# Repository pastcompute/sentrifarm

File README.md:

# Farmer Stay In bed?

This is the main git repository for our entry into the 2015 hackaday prize.
For background see [the Sentrifarm project page on hackaday.io](http://hackaday.io/project/4758).

## Hackaday Prize Entry Qualifications

* [Project discussion](https://hackaday.io/project/4758)
* 2-minute [Quarter Final Submission Video](https://www.youtube.com/watch?v=L6NtuzwXCsY)
* Artist [impression](media/ArtisticImpression.png)
* [Project logs](https://hackaday.io/project/4758)
* [System design diagram](media/architecturediagramv0.2.svg)
* [System design - operational concept](OperationalConcept.md)
* [System design - component assembly](ComponentsAndAssembly.md)
* [TODO List](TODO.md)

## Licenses

* Hardware designs released under Creative Commons CC-BY-SA.
* Source code released under GPL v3 except where existing imported components are otherwise identified as being used under other licenses such as MIT, BSD, etc.
* Clipart in diagrams obtained from open / CC license sources : open office gallery, openclipart.com
* Our own photos and diagrams and videos under CC-BY-NC
* We reserve the right to dual-license software that we developed under alternative licenses

### Third party software components incorporated into the repository

* mqttsn-messages.cpp - MIT license

### Third party software components incorporated into the repository as a submodule

* Adafruit arduino sensor library - Apache license
* Adafruit BMP085 library - open source unspecified
* Arduino MQTTSN library - MIT license
* Arduino DHT11 library - MIT license
* Frankenstein & Antares - GPL licensed ESP8266 framework. Note, not actively used at present tie but this may change.

### Third party software components submodules or cloned and binaries cross-compiled during the build

* openwrt - linux distribution - distribution is GPL, components are their respective open source licenses
* c-ares - library used by mosquitto; MIT license
* mosquitto - MQTT client tools and library; used under Eclipse Distribution License (not the EPL)
* mqtt-sn-tools - MQTT-SN client tools; BSD-like license
* RSMB - MQTT and MQTT-SN broker; Eclipse Distribution License
* libsocket++ - C++ socket library; BSD license

The following third party software components are then dynamically linked to sentrifarm software:

libmosquitto - dynamically linked, thus used as allowed under the terms of the EDLv1.0

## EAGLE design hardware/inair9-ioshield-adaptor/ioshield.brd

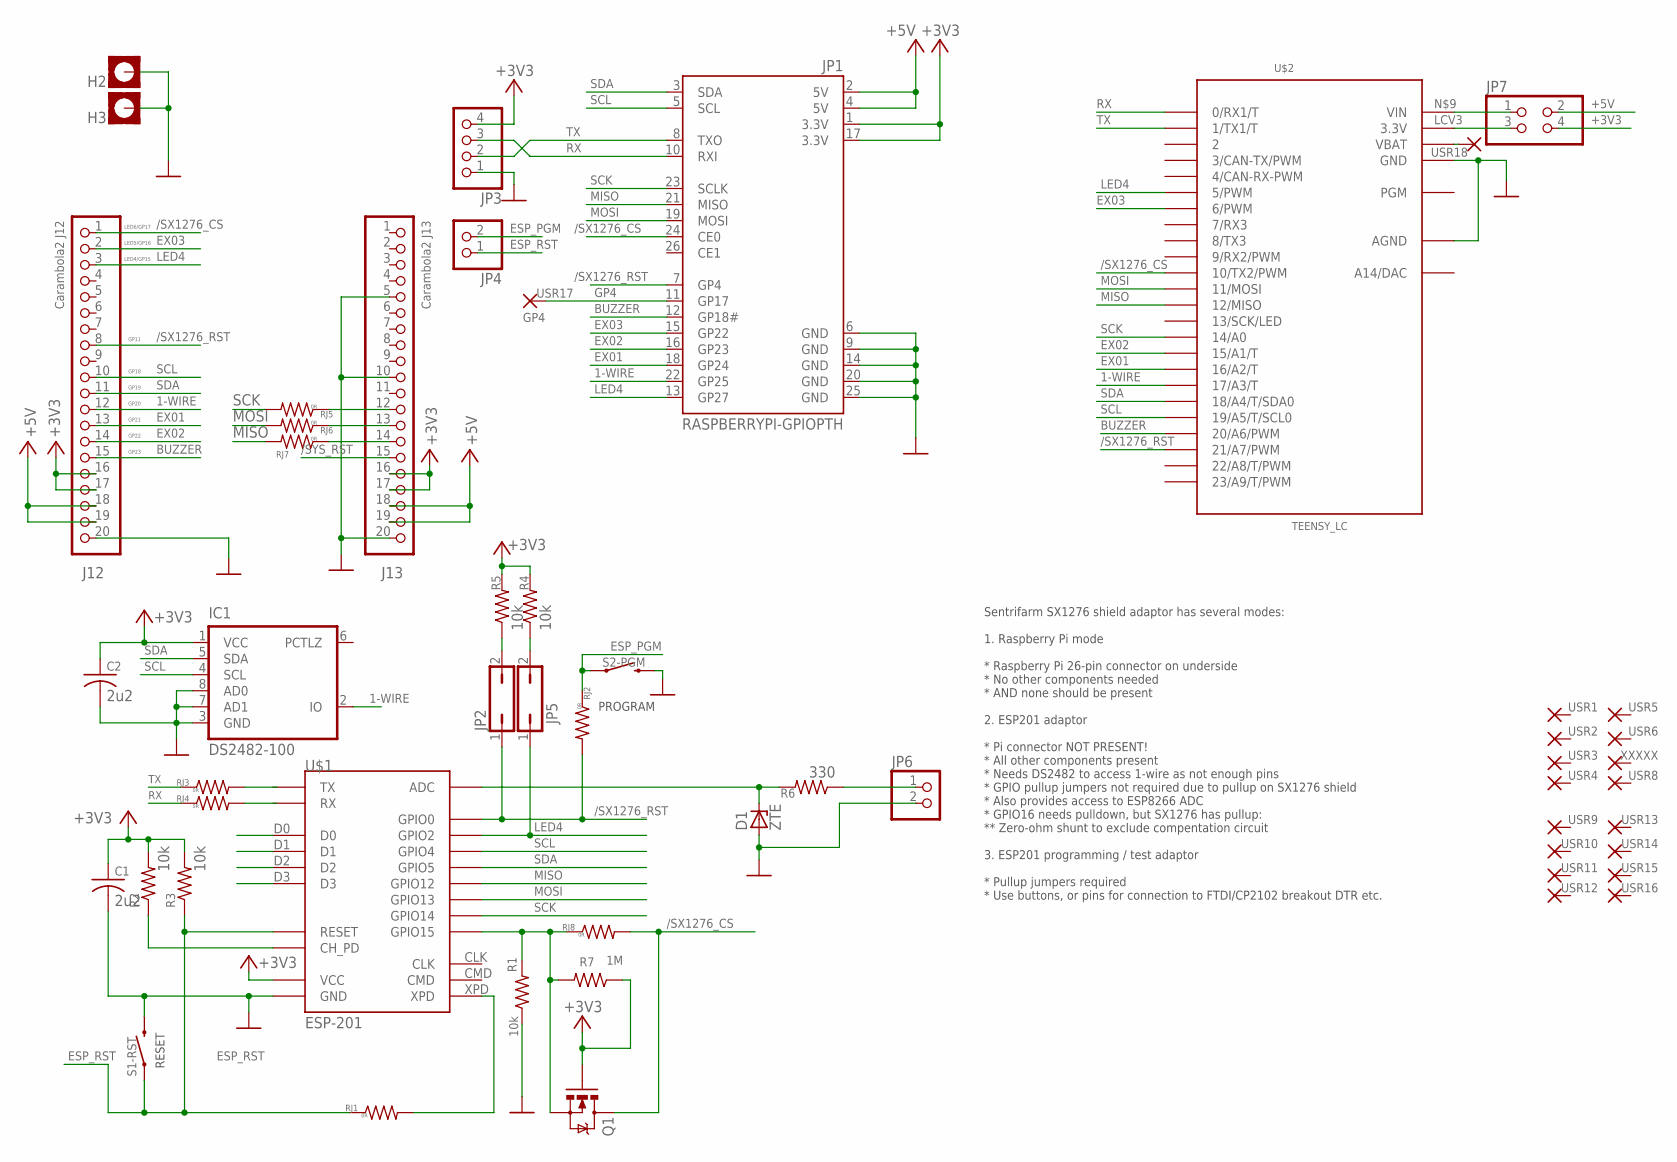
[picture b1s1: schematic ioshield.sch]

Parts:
C1, C2: 2u2; C1206
D1: ZTE; DO35Z10
H2, H3: MOUNT-PAD-SQUARE3.2; 3,2-PAD-SQUARE
IC1: DS2482-100; SO08
J12: Carambola2 J12; 1X20
J13: Carambola2 J13; 1X20
JP1: RASPBERRYPI-GPIOPTH; 2X13-SHROUDED
JP2, JP5: JP1Q; JP1
JP3: PINHD-1X4; 1X04
JP4, JP6: PINHD-1X2; 1X02
JP7: PINHD-2X2; 2X02
Q1: MOSFET-NCHANNEL2N7000; TO-92
R1, R2, R3, R4, R5: 10k; M1206
R6: 330; M1206
R7: 1M; M1206
RJ1, RJ2, RJ3, RJ4, RJ5, RJ6, RJ7, RJ8: 0R; M1206
S1-RST, S2-PGM: SWITCH-MOMENTARY-2PTH; TACTILE-PTH
U$1: ESP-201
U$2: TEENSY_LC; TEENSY_3.1_BASIC
USR1, USR2, USR3, USR4, USR5, USR6, USR8, USR9, USR10, USR11, USR12, USR13, USR14, USR15, USR16, USR18: 1,6/0,8
USR17: GP4; 1,6/0,8
XXXXX: 1,6/0,8

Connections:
1-WIRE: IC1.2 (IO), J12.12, JP1.22 (GP25), U$2.17/A3 (17/A3/T)
+3V3: C1.1, C2.1, IC1.1 (VCC), J12.16, J12.17, J13.16, J13.17, JP1.1 (3.3V), JP1.17 (3.3V), JP3.4, JP7.4, Q1.2 (G), R2.2, R3.2, R4.2, R5.2, R7.1, U$1.3V3 (VCC), U$1.3V3_2 (VCC), U$1.3V3_3 (VCC)
+5V: J12.18, J12.19, J13.18, J13.19, JP1.2 (5V), JP1.4 (5V), JP7.2
/SX1276_CS: J12.1, JP1.24 (CE0), Q1.3 (D), RJ8.2, U$2.10 (10/TX2/PWM)
/SX1276_RST: J12.8, JP1.7 (GP4), JP2.1, RJ2.2, U$1.GPIO0, U$2.21/A7 (21/A7/PWM)
/SYS_RST: J13.15
BUZZER: J12.15, JP1.12 (GP18#), U$2.20/A6 (20/A6/PWM)
CH_PD: R2.1, U$1.CH_PD
ESP_ADC: D1.C, R6.2, U$1.ADC
ESP_GPIO15: Q1.1 (S), R1.2, R7.2, RJ8.1, U$1.GPIO15
ESP_PGM: JP4.2, RJ2.1, S2-PGM.1
ESP_RST: JP4.1, R3.1, RJ1.1, S1-RST.1, U$1.RST (RESET)
EX01: J12.13, JP1.18 (GP24), U$2.16/A2 (16/A2/T)
EX02: J12.14, JP1.16 (GP23), U$2.15/A1 (15/A1/T)
EX03: J12.2, JP1.15 (GP22), U$2.6 (6/PWM)
GND: C1.2, C2.2, D1.A, H2.B3,2, H3.B3,2, IC1.3 (GND), IC1.7 (AD1), IC1.8 (AD0), J12.20, J13.5, J13.10, J13.20, JP1.6 (GND), JP1.9 (GND), JP1.14 (GND), JP1.20 (GND), JP1.25 (GND), JP3.1, JP6.2, R1.1, S1-RST.3 (2), S2-PGM.3 (2), U$1.GND, U$1.GND_2 (GND), U$1.GND_3 (GND), U$2.AGND, U$2.GND, U$2.GND1 (GND)
GP4: JP1.11 (GP17), USR17.1
LCV3: JP7.3, U$2.3.3V, U$2.3.3V1 (3.3V)
LED4: J12.3, JP1.13 (GP27), JP5.1, U$1.GPIO2, U$2.5 (5/PWM)
MISO: JP1.21 (MISO), RJ7.2, U$1.GPIO12, U$2.12 (12/MISO)
MOSI: JP1.19 (MOSI), RJ6.2, U$1.GPIO13, U$2.11 (11/MOSI)
unnamed: JP2.2, R5.1
unnamed: JP5.2, R4.1
unnamed: JP6.1, R6.1
unnamed: U$2.VBAT, USR18.1
unnamed: JP7.1, U$2.VIN
NXXX1: J13.12, RJ5.1
NXXX2: J13.13, RJ6.1
NXXX3: J13.14, RJ7.1
RX: JP1.10 (RXI), JP3.3, RJ4.1, U$2.0 (0/RX1/T)
SCK: JP1.23 (SCLK), RJ5.2, U$1.GPIO14, U$2.14/A0
SCL: IC1.4 (SCL), J12.10, JP1.5 (SCL), U$1.GPIO4, U$2.19/A5 (19/A5/T/SCL0)
SDA: IC1.5 (SDA), J12.11, JP1.3 (SDA), U$1.GPIO5, U$2.18/A4 (18/A4/T/SDA0)
TX: JP1.8 (TXO), JP3.2, RJ3.1, U$2.1 (1/TX1/T)
XPD: RJ1.2, U$1.XPD

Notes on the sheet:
LED6/GP17
GP18
GP19
GP20
GP21
GP22
GP23
LED5/GP16
LED4/GP15
GP11
Sentrifarm SX1276 shield adaptor has several modes: 1. Raspberry Pi mode * Raspberry Pi 26-pin connector on underside * No other components needed * AND none should be present 2. ESP201 adaptor * Pi connector NOT PRESENT! * All other components present * Needs DS2482 to access 1-wire as not enough 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
PROGRAM
RESET

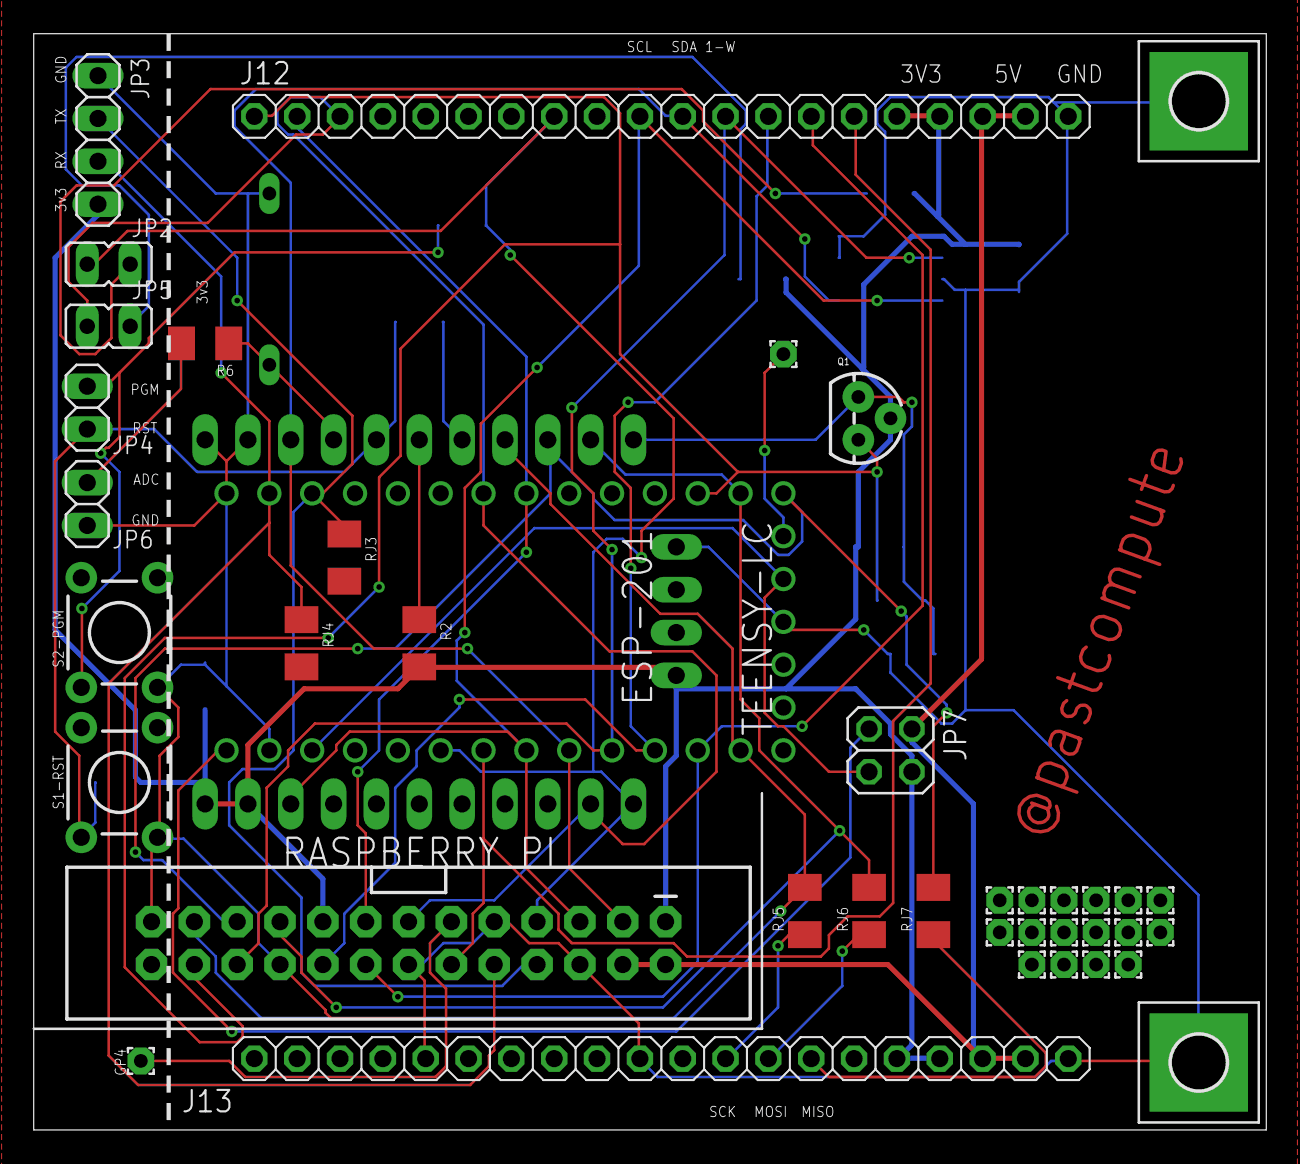
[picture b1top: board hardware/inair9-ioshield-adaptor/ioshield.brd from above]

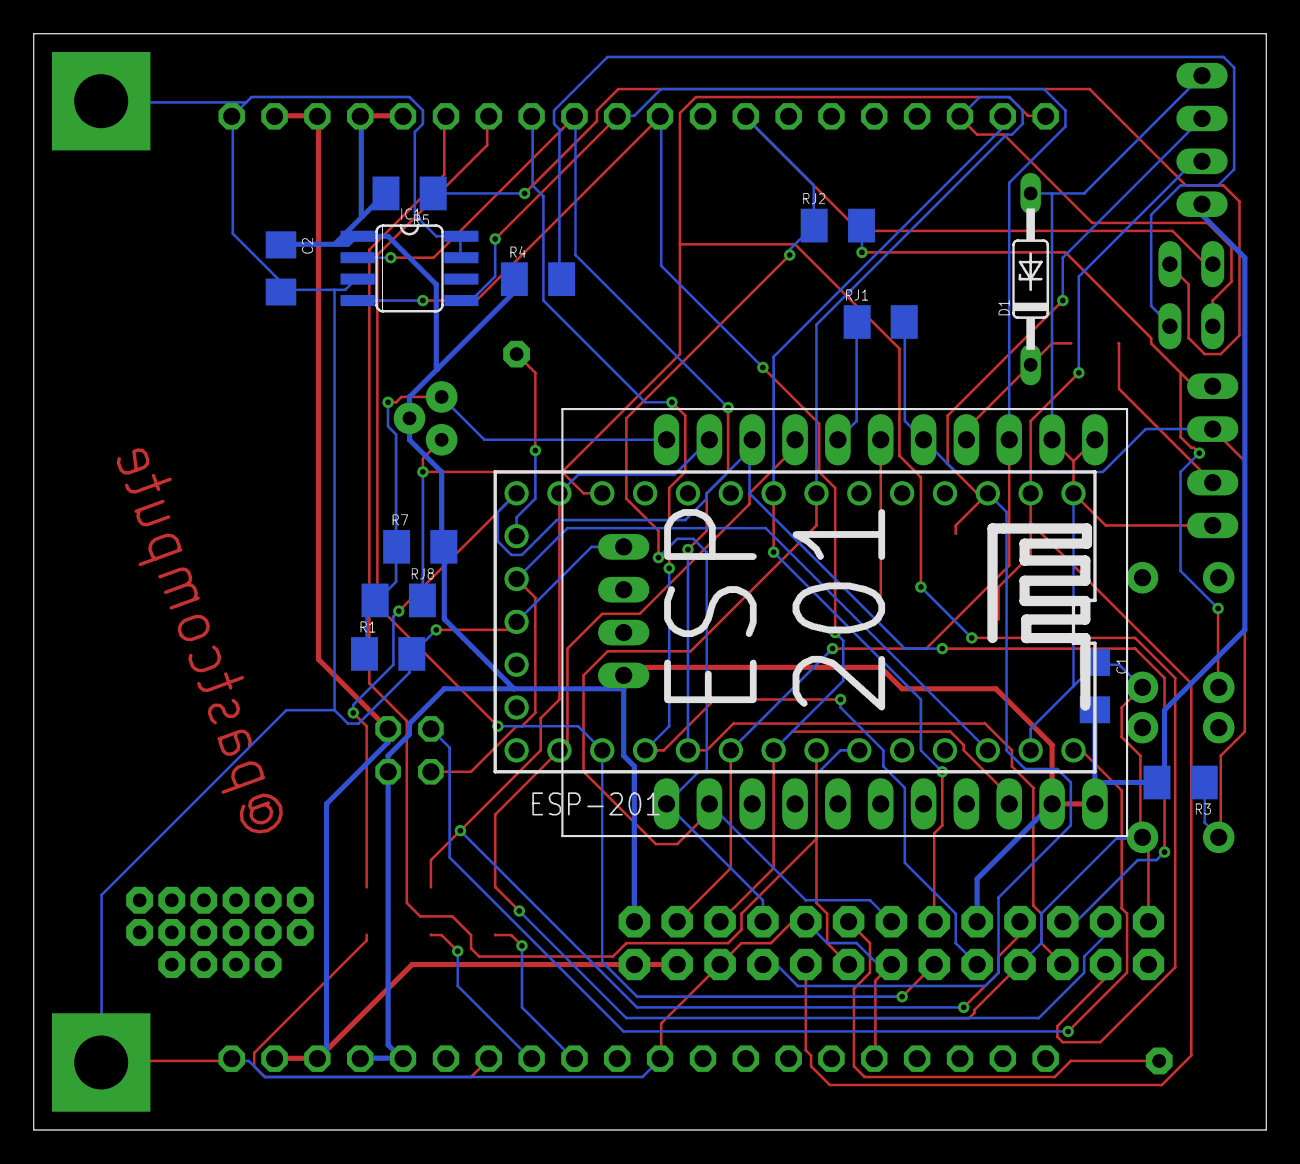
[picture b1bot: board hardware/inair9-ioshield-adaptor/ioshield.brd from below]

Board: 2 copper layers, 73.1 x 65.0 mm, 53 parts (14 on the bottom side), 34 nets.

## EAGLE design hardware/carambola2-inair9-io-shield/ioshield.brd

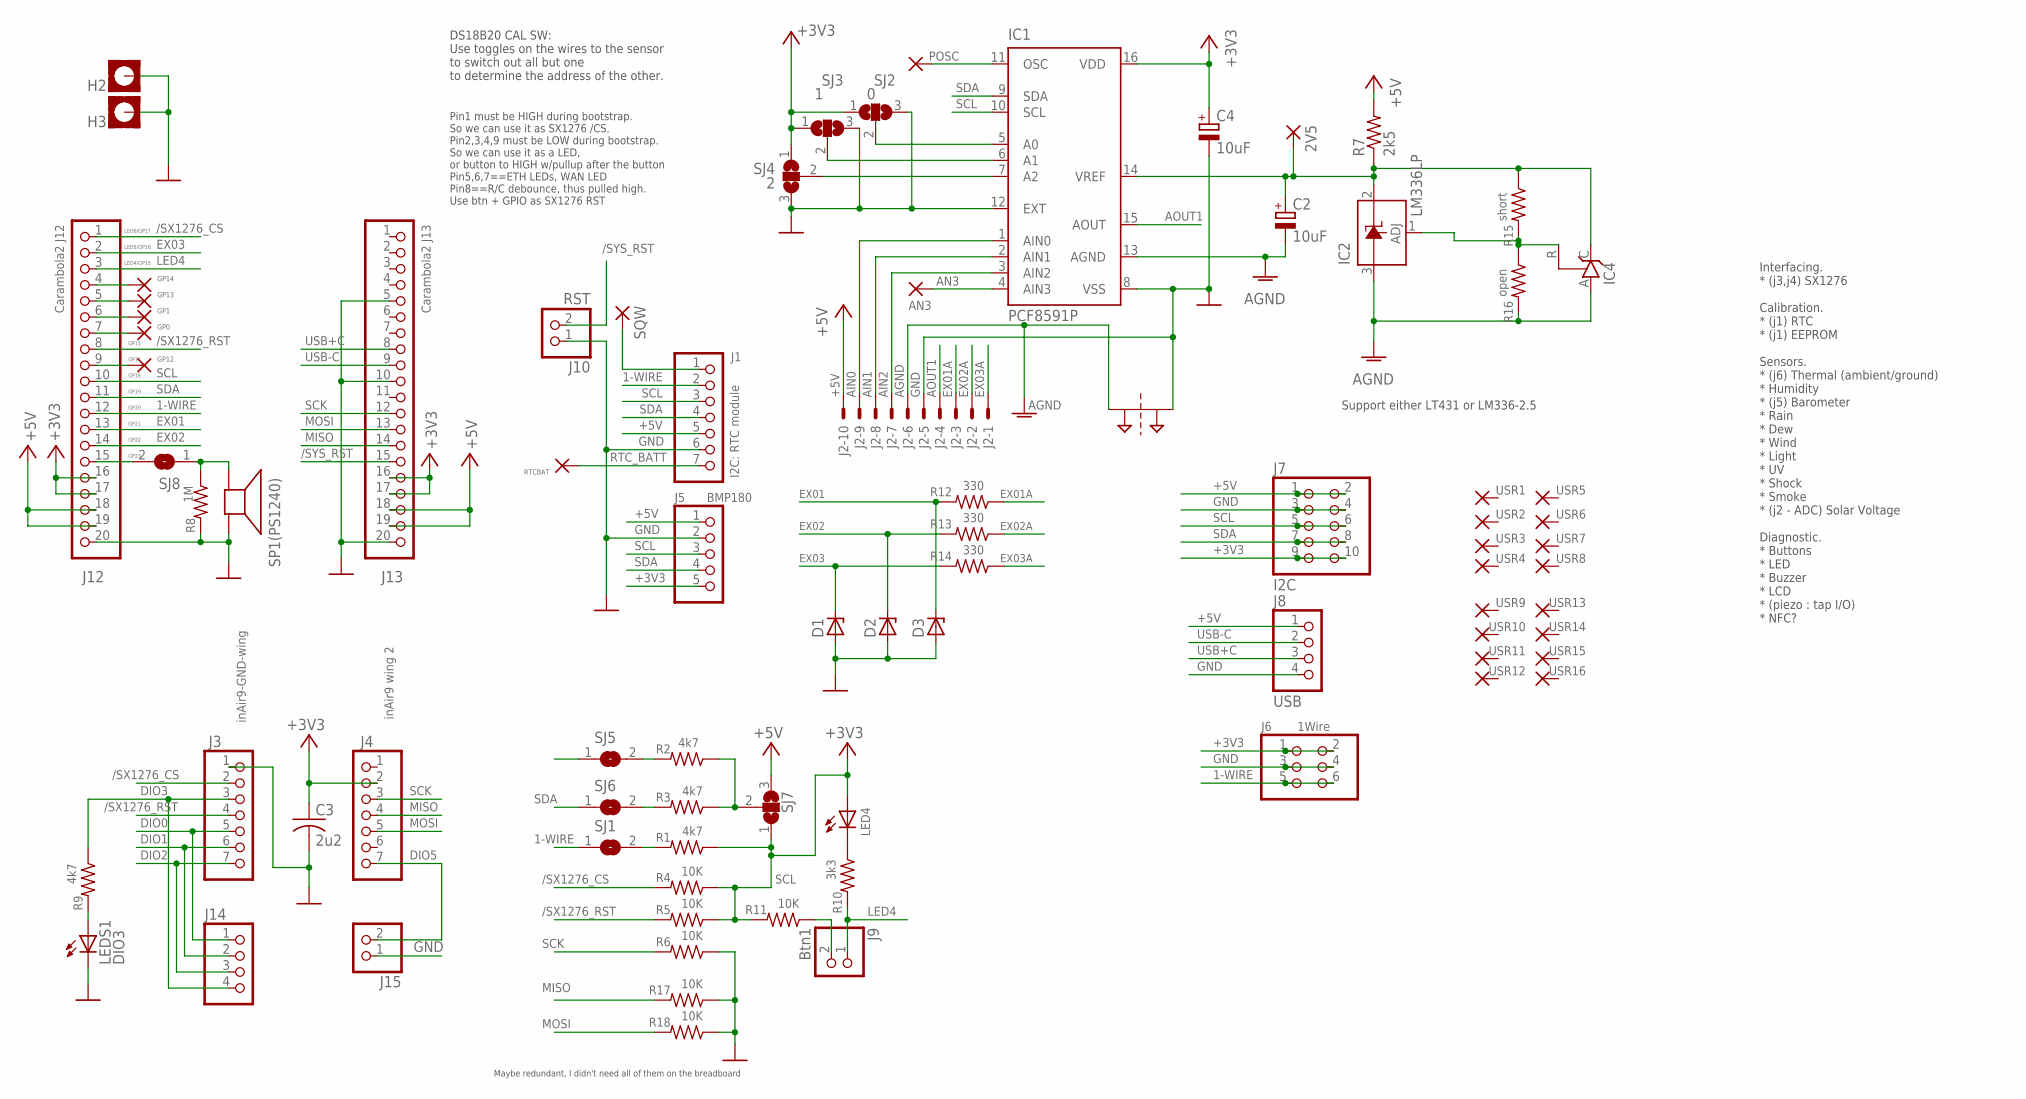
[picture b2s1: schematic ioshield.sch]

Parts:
2V5: 2,54/0,8
AN3: AN3; 2,54/0,8
C2, C4: 10uF; E2,5-5
C3: 2u2; C1206
D1, D2, D3: ZENER-DIODEZD-2.5; ZDIO-2.5
GP0, GP1, GP12, GP13, GP14: 2,54/0,8
H2, H3: MOUNT-PAD-SQUARE3.2; 3,2-PAD-SQUARE
IC1: PCF8591P; DIL16
IC2: LM336LP; TO92
IC4: TL431CLP; TO92-CLP
J1: I2C: RTC module; 1X07
J2: 22-23-2101; MPN Screw Terminal
J3: inAir9-GND-wing; 1X07
J4: inAir9 wing 2; 1X07
J5: BMP180; 1X05
J6: 1Wire; 2X03
J7: I2C; 2X05
J8: USB; 1X04
J9: Btn1; 1X02
J10: RST; 1X02
J12: Carambola2 J12; 1X20
J13: Carambola2 J13; 1X20
J14: PINHD-1X4; 1X04
J15: PINHD-1X2; 1X02
LED4: LED3MM
LEDS1: DIO3; LED3MM
POSC: 2,54/0,8
PT1: 2PT_GND_TIE
R1, R2, R3, R9: 4k7; M1206
R4, R5, R6, R11, R17, R18: 10K; M1206
R7: 2k5; M1206
R8: 1M; M1206
R10: 3k3; M1206
R12, R13, R14: 330; M1206
R15: short; M1206
R16: open; M1206
RTCBAT: 2,54/0,8
SJ1, SJ5, SJ6, SJ8: SJ
SJ2: 0; SJ_2
SJ3: 1; SJ_2
SJ4: 2; SJ_2
SJ7: SJ2W; SJ_2
SP1(PS1240): SPEAKER/AL11P; AL11P
SQW: 2,54/0,8
USR1, USR2, USR3, USR4, USR5, USR6, USR7, USR8, USR9, USR10, USR11, USR12, USR13, USR14, USR15, USR16: 1,6/0,8

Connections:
1-WIRE: J1.2, J6.5, J6.6, J12.12, SJ1.1
+3V3: C3.1, C4.+, IC1.16 (VDD), J4.2, J5.5, J6.1, J6.2, J7.9, J7.10, J12.16, J12.17, J13.16, J13.17, LED4.A, R1.1, R4.1, R5.1, R11.2, SJ2.1, SJ3.1, SJ4.1, SJ7.1
+5V: J1.5, J2.10, J5.1, J7.1, J7.2, J8.1, J12.18, J12.19, J13.18, J13.19, R7.2, SJ7.3
/SX1276_CS: J3.2, J12.1, R4.2
/SX1276_RST: J3.4, J12.8, R5.2
/SYS_RST: J10.2, J13.15
AGND: C2.-, IC1.13 (AGND), IC2.3 (A), IC4.A, J2.6, PT1.P$1, R16.2
AIN0: IC1.1 (AIN0), J2.9
AIN1: IC1.2 (AIN1), J2.8
AIN2: IC1.3 (AIN2), J2.7
AIN3: AN3.1, IC1.4 (AIN3)
AOUT1: IC1.15 (AOUT), J2.4
DIO0: J3.5, J14.1
DIO1: J3.6, J14.2
DIO2: J3.7, J14.3
DIO3: J3.3, J14.4, R9.1
DIO5: J4.7, J15.2
EX01: D3.C, J12.13, R12.2
EX01A: J2.3, R12.1
EX02: D2.C, J12.14, R13.2
EX02A: J2.2, R13.1
EX03: D1.C, J12.2, R14.2
EX03A: J2.1, R14.1
GND: C3.2, C4.-, D1.A, D2.A, D3.A, H2.B3,2, H3.B3,2, IC1.8 (VSS), IC1.12 (EXT), J1.6, J2.5, J3.1, J5.2, J6.3, J6.4, J7.3, J7.4, J8.4, J10.1, J12.20, J13.5, J13.10, J13.20, J15.1, LEDS1.K (C), PT1.P$2, R6.1, R8.2, R17.1, R18.1, SJ2.3, SJ3.3, SJ4.3, SP1(PS1240).-
LED4: J9.1, J12.3, R10.2
MISO: J4.4, J13.14, R17.2
MOSI: J4.5, J13.13, R18.2
unnamed: IC2.1 (ADJ), IC4.R, R15.2, R16.1
unnamed: R2.1, R3.1, SJ7.2
unnamed: IC1.11 (OSC), POSC.1
unnamed: J9.2, R11.1
unnamed: R1.2, SJ1.2
unnamed: GP12.1, J12.9
unnamed: GP14.1, J12.4
unnamed: R2.2, SJ5.2
unnamed: R8.1, SJ8.1, SP1(PS1240).+
unnamed: IC1.7 (A2), SJ4.2
unnamed: R3.2, SJ6.2
unnamed: GP0.1, J12.7
unnamed: LED4.K (C), R10.1
unnamed: J1.1, SQW.1
unnamed: IC1.5 (A0), SJ2.2
unnamed: LEDS1.A, R9.2
unnamed: J12.15, SJ8.2
unnamed: IC1.6 (A1), SJ3.2
unnamed: GP1.1, J12.6
unnamed: GP13.1, J12.5
RTC_BATT: J1.7, RTCBAT.1
SCK: J4.3, J13.12, R6.2
SCL: IC1.10 (SCL), J1.3, J5.3, J7.5, J7.6, J12.10, SJ5.1
SDA: IC1.9 (SDA), J1.4, J5.4, J7.7, J7.8, J12.11, SJ6.1
USB+C: J8.3, J13.8
USB-C: J8.2, J13.9
VREF2V5: 2V5.1, C2.+, IC1.14 (VREF), IC2.2 (C), IC4.C, R7.1, R15.1

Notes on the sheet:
LED6/GP17
GP18
GP19
GP20
Interfacing. * (j3,j4) SX1276 Calibration. * (j1) RTC * (j1) EEPROM Sensors. * (j6) Thermal (ambient/ground) * Humidity * (j5) Barometer * Rain * Dew * Wind * Light * UV * Shock * Smoke * (j2 - ADC) Solar Voltage Diagnostic. * Buttons * LED * Buzzer * LCD * (piezo : tap I/O) * NFC?
DS18B20 CAL SW: Use toggles on the wires to the sensor to switch out all but one to determine the address of the other.
Pin1 must be HIGH during bootstrap. So we can use it as SX1276 /CS. Pin2,3,4,9 must be LOW during bootstrap. So we can use it as a LED, or button to HIGH w/pullup after the button Pin5,6,7==ETH LEDs, WAN LED Pin8==R/C debounce, thus pulled high. Use btn + GPIO as SX1276 RST
GP21
GP22
GP23
LED5/GP16
LED4/GP15
GP11
GP12
Support either LT431 or LM336-2.5
Maybe redundant, I didn't need all of them on the breadboard

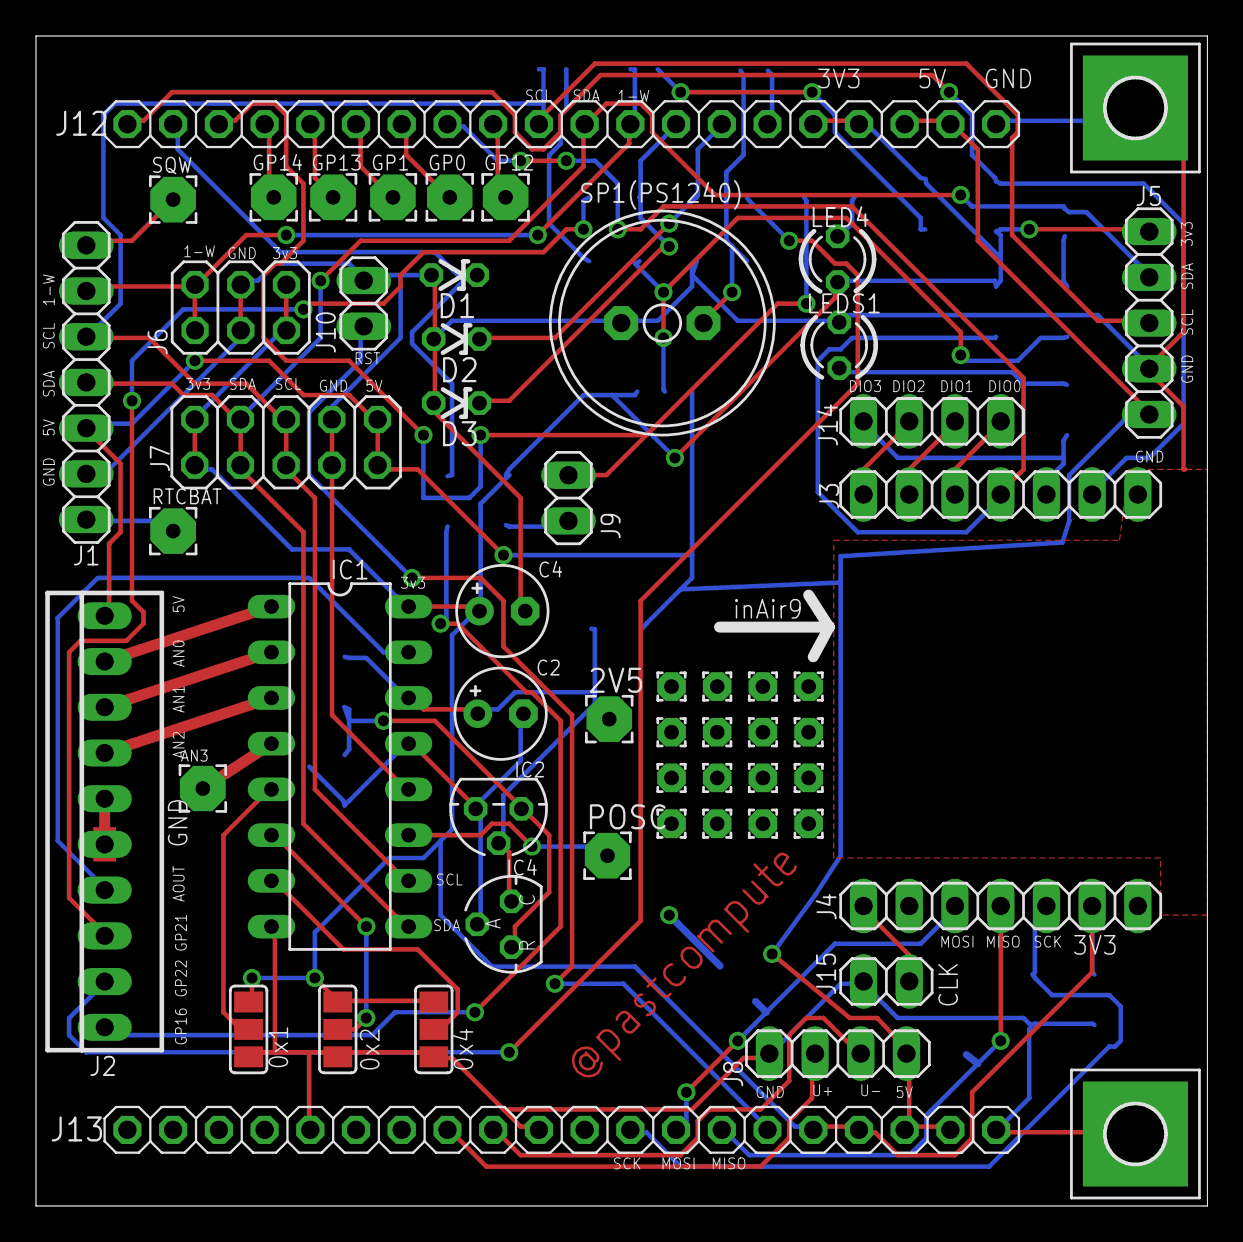
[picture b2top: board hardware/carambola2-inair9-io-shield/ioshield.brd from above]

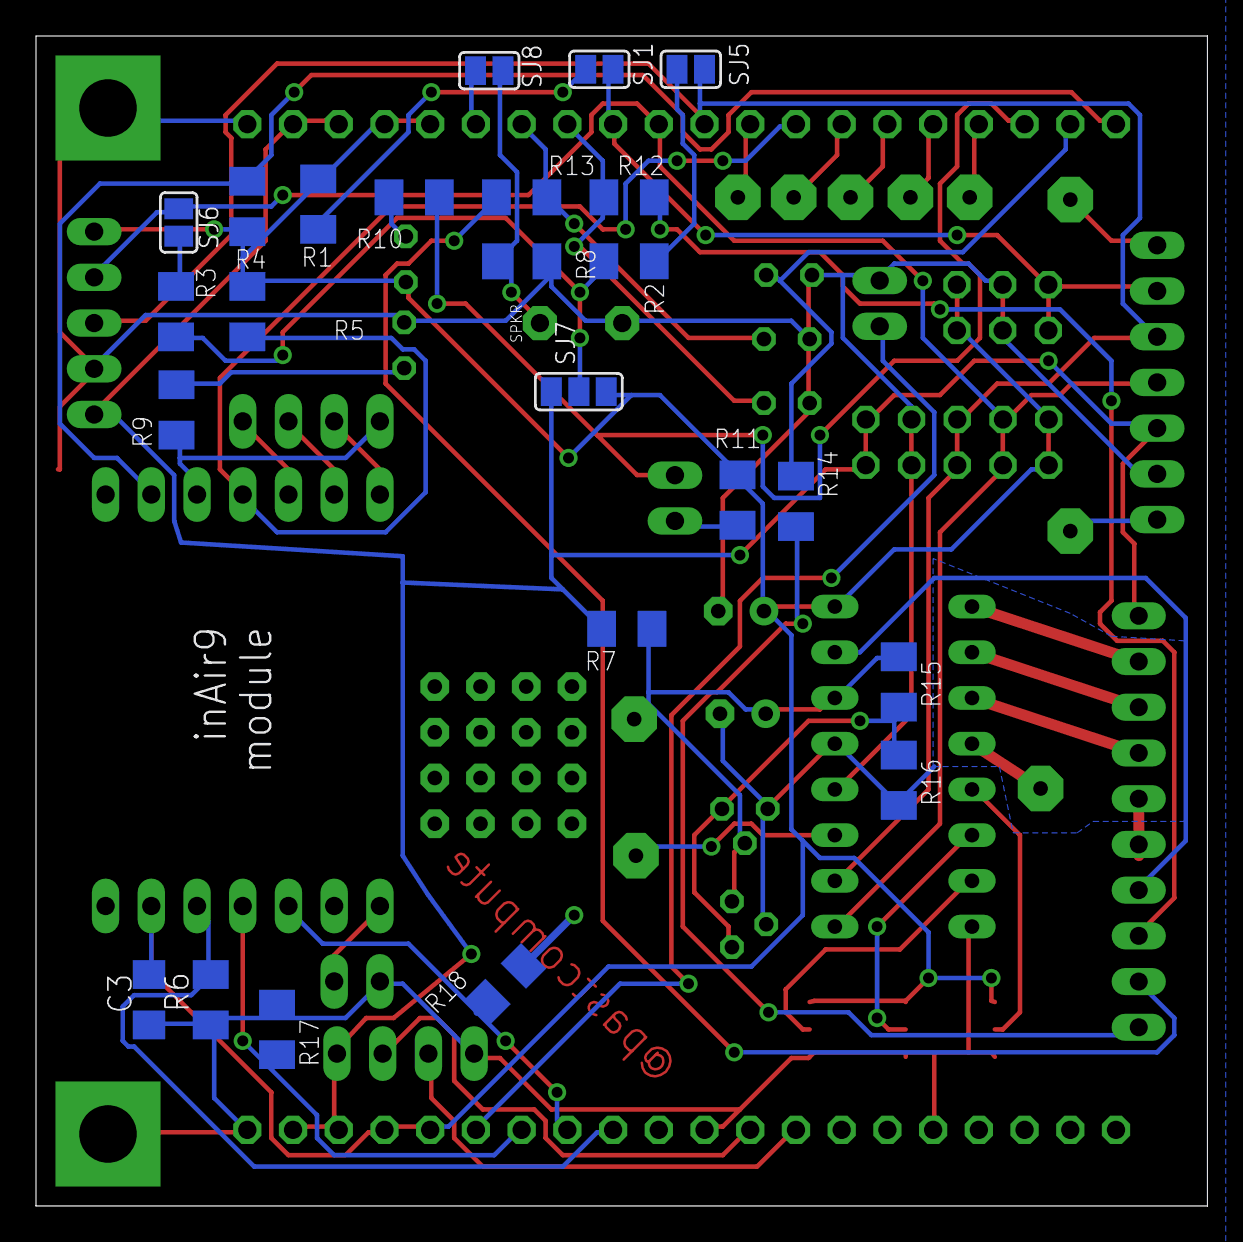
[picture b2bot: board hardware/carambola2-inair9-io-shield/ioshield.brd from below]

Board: 2 copper layers, 65.1 x 65.0 mm, 81 parts (24 on the bottom side), 54 nets.

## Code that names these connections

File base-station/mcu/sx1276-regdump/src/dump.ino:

#include "Arduino.h"
#include <SPI.h>

// Supports the following configurations:
//
// (1) ESP8266, using sentrifarm-shield-adaptor
//     GPIO12 = MISO (HSPI)
//     GPIO13 = MOSI (HSPI)
//     GPIO14 = SCK (HSPI)
//     GPIO15 = CS
//     GPIO0  = RST
//     GPIO2  = LED4 (inverted)
//
// (2) TEENSY LC, using sentrifarm-shield-adaptor
//     MOSI,11
//     MISO,12
//     SCK,14
//     CS,10
//     RST,21
//     LED4,5

#if defined(ESP8266)
#include <Esp.h> // deep sleep
#define PIN_LED4         4
#define PIN_SX1276_RST   0
#define PIN_SX1276_CS   15
#define PIN_SX1276_MISO 12
#define PIN_SX1276_MOSI 13
#define PIN_SX1276_SCK  14
#elif defined(TEENSYDUINO)
#define PIN_LED4         5
#define PIN_SX1276_RST  21
#define PIN_SX1276_CS   10
#define PIN_SX1276_MISO 12
#define PIN_SX1276_MOSI 11
#define PIN_SX1276_SCK  14
#else
#error "Unsupported configuration"
#endif

SPISettings spiSettings(1000000, MSBFIRST, SPI_MODE0); // double check

void setup()
{
  Serial.begin(115200);
  Serial.println("Sentrifarm : sx1276 register dump");

  pinMode(PIN_LED4,        OUTPUT);
  pinMode(PIN_SX1276_RST,  OUTPUT);
  pinMode(PIN_SX1276_CS,   OUTPUT);

  // Power on the LED (active low2)
  digitalWrite(PIN_LED4, LOW);

#if defined(TEENSYDUINO)
  SPI.setSCK(PIN_SX1276_SCK);
#endif

  digitalWrite(PIN_SX1276_CS, HIGH);
  digitalWrite(PIN_SX1276_RST, HIGH);
  digitalWrite(PIN_SX1276_MISO, HIGH);
  digitalWrite(PIN_SX1276_MOSI, HIGH);
  digitalWrite(PIN_SX1276_SCK,  HIGH);

}


void loop() {

  digitalWrite(PIN_LED4, LOW);
	SPI.begin();

  // Reset the sx1276
  digitalWrite(PIN_SX1276_RST, LOW);
  delay(10); // spec states to pull low 100us then wait at least 5 ms
  digitalWrite(PIN_SX1276_RST, HIGH);
  delay(50);

  char buf[4];
  for (byte r=0; r <= 0x70; r++) {
    if (r % 8 == 0) {
      snprintf(buf, sizeof(buf), "%02x ", r);
      Serial.print(buf);
    }
    SPI.beginTransaction(spiSettings);
    digitalWrite(PIN_SX1276_CS, LOW);
    SPI.transfer(r);
    byte value = SPI.transfer(0);
    digitalWrite(PIN_SX1276_CS, HIGH);
    SPI.endTransaction();
    snprintf(buf, sizeof(buf), "%02x ", value);
    Serial.print(buf);
    if (r % 8 == 7) { Serial.println(); }
  }
  Serial.println();

  delay(100);

	SPI.end();
  digitalWrite(PIN_LED4, HIGH);

#if defined(ESP8266)
  Serial.println("Request deep sleep");
	// ESP.deepSleep(8000000, WAKE_RF_DEFAULT); // long enough to see current fall on the USB power meter
	ESP.deepSleep(8000000, WAKE_RF_DISABLED); // long enough to see current fall on the USB power meter
	delay(500);
  Serial.println("Requested deep sleep"); // we should not ever see this
#else
	// FIXME
	delay(7000);
#endif
}

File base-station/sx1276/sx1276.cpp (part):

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  // TODO: Report node address

  // DIO mapping
  // mapping 1 bits 6..7 DIO0
  // mapping 1 bits 4..5 DIO1
  // mapping 1 bits 2..3 DIO2
  // mapping 1 bits 0..1 DIO3
  // mapping 2 bits 6..7 DIO4
  // mapping 2 bits 4..5 DIO5
  // mapping 2 bits 0 - 1 = multiplex preambledetect 0 = multiplex rssi

  // LED on DIO3 : Valid header : 01
  // Pin header DIO5 : Clk Out: 10
  // Pin header DIO1 : Rx timeout: 00
  // Pin header DIO0 : Tx done: 01

  spi_->ReadRegister(SX1276REG_DioMapping1, v);
  WriteRegisterVerify(SX1276REG_DioMapping1, v | 0x1);
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
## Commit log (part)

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2015-03-28 Initial commit.
2015-03-28 Save bare as bare
2015-03-28 Resturcture sensor code hierarchy
2015-03-28 Create absolute bare minimum nateive firmware
2015-03-28 ESP + DHT : should be working, but doesnt due to electrical issues
2015-03-28 Initial commit for ESP8266 application skeleton using antares
2015-03-28 Port fixes from minimal
2015-03-28 Track .config for this specific application
2015-03-28 Working start wifi scan
2015-03-28 Move initial ESP play to experiments directory
2015-03-28 Make a minimum viable config
2015-03-28 More build setup
2015-03-28 Updated to my frankenstein autoconnect patch
2015-03-28 Operational hello world for sentrifarm
2015-03-29 Working TCP push ds18b20 temperature
2015-04-05 fix typos
2015-04-05 A demo circuit for ESP monitoring
2015-04-05 Preliminary circuit for solar performance monitor
2015-04-05 First draft data solar data logger
2015-04-05 Tidy arduino code
2015-04-06 simulation mode
2015-04-10 Resynchronise upstream frankenstein
2015-04-10 Solar logging runs
2015-04-15 Mostly implement draft sensor code state machine, ready to hook up to sensor and try with solar panel
2015-04-16 Working non-deep-sleep logger
2015-04-17 Log tick count
2015-04-17 Lets try 1/2 hour intervals now
2015-04-18 Some code cleanup, before moving on to more detailed design
2015-04-18 Whitespace fixes
2015-04-18 A better way to link with frankenstein, reduces patch by 1
2015-04-19 Deep sleep tweaks
2015-04-20 Updated frankenstein submodule
2015-04-20 Setup a router to act as a pretend base station
2015-04-20 Script for router dataligging
2015-04-25 Work inprogress
2015-04-25 frank
2015-04-25 Test that demonstrates failed wifi after deep sleep wakeup
2015-04-25 Work in progress
2015-04-25 stackdumper
2015-04-28 Base stattion prototype: carambola with i2c pressure sensor and RTC, and SPI for LoRa
2015-04-28 Forgot the ground sensor schematic
2015-04-29 SPI working
2015-04-29 Code to read LoRa SX1276 ver
2015-04-29 Bus pirate commands
2015-05-01 Minor tidyup of sx1276 reg dump
2015-05-01 Build stuff for carambola2
2015-05-03 Tested working SPI to sx1276 on carambola using ar933x SPI
2015-05-11 Schematic and PCB board for Carambola2 inAir9 I/O shield
2015-05-12 Schematics as provided to OshPark
2015-05-13 C++ library skeleton for SX1276 module
2015-05-14 Tested buspirate C++ skeleton
2015-05-14 spidev register read code
2015-05-14 Tidy up duplicate code
2015-05-14 Decouple bus pirate powerup from SPI config
2015-05-14 Enter LoRa mode using BusPirate
2015-05-15 Setup carrier frequency
2015-05-15 Enough precision to report carrier
2015-05-16 Register setup for tx
2015-05-17 Working beacon tx\!
2015-05-17 Increased robustness of beacon
2015-05-18 Write register for spidev
2015-05-18 Fix test program running on carambola
2015-05-18 Build infrastructure for building sx1276 code with OpenWRT
2015-05-18 Script for checking which patches are applied to openwrt
2015-05-19 Openwrt boost libraries
2015-05-19 First cut at basic receive functionality
2015-05-19 Tested receive, Works on Linux SPI, bus pirate is flaky
2015-05-19 fcn for masked write on read
2015-05-19 Note about bus pirate
2015-05-19 Added optional debug macro
2015-05-19 Code to trace through state changes
2015-05-20 Remove inadvertent IRQ flag setting error
2015-05-20 Code todyup
2015-05-20 Seems to be reliably receving beacon. Some tidy up required, possibly issue with BP reset
2015-05-20 Counting message:
2015-05-20 Reset frequency on power off
2015-05-23 Minor whitespace
2015-05-24 Big tidy up, decouple SPI from platform (gpio, reset)
2015-05-27 Really simple dumb all-client
2015-05-27 Start on mqtt client class
2015-05-29 C++ wrapper for mqtt client - subscriber
2015-05-30 Minor cleanup
2015-06-01 Update file licenses
2015-06-03 Fixes to build mosquitto and c-ares for openwrt
2015-06-04 Conclude present mqtt-sn socat bridge experiment
2015-06-04 Update 3rd party linked library license information
2015-06-04 Update project planning
2015-06-04 Import submodule for libsocket
2015-06-05 Two way bridge over socat pipe
2015-06-06 Swap SCL, SDA due to PCB error
2015-06-06 Working remote subscribe
2015-06-06 LED is on GPIO15. Also add beeper module
2015-06-06 Fix openwrt build issues
2015-06-06 First cut at sx1276 mqttsn bridge
2015-06-06 Program to dump regs on spidev
2015-06-07 Fix stupid locking error
2015-06-07 Worlds dodgiest layer 2 protocol but it works
2015-06-07 Messages flowing now, just need to sort out RSMB. Probably we should drop the ACK code, because getting cross inteference and MQTT-SN does it anyway Also fixed spurious byte which was causing problem
2015-06-08 Cross compile mqtt-sn-tools for openwrt
2015-06-08 Refactor and cleanup the radio bridge, drop ACK code
2015-06-08 Finally, mqtt-sn traversing sx1276 radio link
2015-06-08 Improved relative layer2 reliability by xor'ing packets - it seems we can get corruption even when CRC allegedly good?
2015-06-19 Setup to use platformio for mcu-based nodes
2015-06-19 SX1276 MCU register dump
2015-06-21 Platformio working hello world on ESP. Todo: teensy
2015-06-21 ESP8266 can read registers of SX1276 now
2015-06-21 Restructure to prepare to support raspberry pi target as well
2015-06-23 SPI device for raspi
2015-06-24 Update libsocket patche
2015-06-27 Schematic and PCB for the shield adaptor
2015-06-27 Circuit PDFs
2015-06-27 qtcreator find include dirs
2015-06-28 Beacon using the sx1272 lib for a quick start
2015-06-28 Attempt to use sx1272 as arduino lib no good, too large for icache and a PITA to fix. Time to (re)write my own
2015-06-28 Code for SX1276 beacon on esp8266/teensy/arduino
2015-06-30 Ready to test ESP8266 beacon
2015-06-30 Working beacon on ESP8266 + SX1276
2015-07-01 Update beacon wrt rx
2015-07-01 Working receiver with low message loss c/f bus pirate (yay) next : MCU version of MQTT-SN
2015-07-06 Minor tidy
2015-07-06 Async mqttsn lib
2015-07-11 Import mqtt-sn-arduino forked from https://bitbucket.org/MerseyViking/mqtt-sn-arduino/src commit 0d00d95261319c40ffa19d81f33b3bc3aa767be7
2015-07-11 Tweak up arduino mqtt sn fork to work how we need it
2015-07-11 Rough cut of SX1276 MQTTSN node on Arduino / Teenst / ESP8266
2015-07-11 Make the radio code fit into ESP8266 memory
2015-07-11 Keep radio warm when receiving repeatedly, otherwise we loose data
2015-07-11 More debugging
2015-07-11 Fix broken return code from other side (attribute pcked)
2015-07-11 Woot! Working mqttsn pub from ESP8266 --> carambola2
2015-07-11 For some reason we were dropping one byte on carambola2
2015-07-12 Extend mqttsn demo to send some stuff read from the MCU chip
2015-07-22 Read i2c pressure / temp / ADC hack test. A2c maybe junk, could be because I havent soldered the address jumpers to ground
2015-08-02 Major restructure and cleanup of directories
2015-08-02 (cleanup) v0 of high level design diagram
2015-08-02 Fix submodules
2015-08-02 Added build and todo documentation
2015-08-02 Update build to work properly, and document Openwrt build process and licenses
2015-08-02 Update todo
2015-08-09 Incorporate changes to concept document
2015-08-15 Updated system architecture diagram
2015-08-17 Update Makefile
2015-08-17 Try with QOS 0
2015-08-17 Fix compiler warning and PTOA for the bridge
2015-08-17 Make bridge and tx test use same preamble
2015-08-17 Media update
2015-08-19 Tweak openwrt build to be able to find our own local feed
2015-08-19 Remove SPI read/write from ESP8266 ICACHE flash to see if it helps performance
2015-08-19 Workaround issues with i2c failing after radio ops
2015-08-19 Spread out tx of publish msgs
2015-08-19 More debugging on linux side
2015-08-19 Bump symbol timeout to 366 same as teensy side
2015-08-22 Fixes to make Qt5/qtserialport build for openwrt
2015-08-23 Fix issues with raspberry pi build
2015-08-23 Experimental platformio builder for openwrt
2015-08-23 Integrate raspi & carabola2 all build
2015-08-23 Restructure MCU libraries
2015-08-23 typo
2015-08-26 Missing symlink
2015-08-26 Restructure & cleanup common code ready for leaf development in earnest
2015-08-26 Tidy of new leaf node firmware, ready to rework the MQTTSN loop
2015-08-29 More refactoring of leaf node code
2015-08-29 Implement RTC read
2015-08-29 Improve i2c debugging
2015-08-29 Report chipset data
2015-08-29 Fix report of git hash (wip)
2015-08-29 Improve stats
2015-08-29 Flesh out MQTTSN payload
2015-08-29 Allow larger MQTTSN payload to be tx
2015-08-29 Revert to QOS0, msgs seem to get stuck on other side
2015-08-29 Increase symbol timeout on Linux side to cope with larger msgs
2015-08-30 Implement jumper selectable beacon mode for testing
2015-08-30 Need date_time for printing timestamp in rx test
2015-08-30 Print time in rx test, and use spinner instead of x's to indicate working
2015-08-30 Dont do things that cause message loss in rx test
2015-08-30 Rejig linux sx1276 mqttsn bridge to work as UDP client as well
2015-09-06 Start improving OpenWRT build with MQTT programs
2015-09-06 Setup mqtt2graphite bridge from MQTT to graphite / grafana
2015-09-06 Import docker container for grafana
2015-09-06 Update to sentrifarm branch of docker for grafana
2015-09-06 Fix RSMB to take 'REVERSED' message byte bitfield
2015-09-11 Got Raspi build working properly again
2015-09-11 Bump dockerfile
2015-09-12 Fix teensy build
2015-09-12 OpenWRT autostart MQTT and radio. Probably needs a watchdog still.
2015-09-13 20dBm mode for leaf node
2015-09-13 20dBm mode for Linux
2015-09-13 Added beacon RX mode for ESP / teensy
2015-09-13 Report linux beacon tx time in beacon message
2015-09-13 Tweak to openwrt build
2015-09-13 TeensyLC working 'deep' sleep
2015-09-13 Fix issue with puback
2015-09-13 Report last SNR instead of rssi
2015-09-13 more flash strings
2015-09-13 Detect jumper for beacon mode on carambola2
2015-09-14 Forgot to update arch diagram last month
2015-09-14 Use beacon mode jumper to reset boot count
2015-09-14 Fix QOS 1
2015-09-14 Improve raspbery pi support
2015-09-15 Document raspbi pinouts
2015-09-15 More pi specific fixes
2015-09-15 Fix openwrt service start
2015-09-15 Improvements to tracing of linux sx1276
2015-09-15 Set high power mode from environment
2015-09-15 Allow trace debug enabled from environment for the bridge, and ensure symbol timeout is activated in test rx
2015-09-15 Dont deep sleep when the MCU is beaconing
2015-09-15 Fix incorrect coding rate setting
2015-09-15 Fix beacon mode for ESP8266
2015-09-15 Fix spurious register write (LNA) in mcu
2015-09-19 Change MQTT topic to include node address, instead of data
2015-09-19 Read 1-wire thermometer in base station
2015-09-19 Improve timeout handling in Linux.
2015-09-19 Issues with i2c on teensy
2015-09-19 Add humidity sensor to paddock node.
2015-09-19 More belt tightening to get it going in the ESP01 again
2015-09-19 Use DHT11 on GPIO2 of the ESP-201
2015-09-20 Slim down the DHT library for the ESP01
2015-09-20 Check radio presence when testing without carrier board
2015-09-20 Artisists impression
2015-12-31 Fix issues with RTC
2015-12-31 Fix issues with humidity sensor
2015-12-31 Fix issuesd with OpenWRT build
2015-12-31 Fix issues with ADC
2016-01-01 Improve handling of repository
2016-01-01 Auto run script
2016-01-01 Use private VPS IP with internal NAT egress
2016-01-01 Minor tweaks
2016-01-01 Remove redundant build flag
2016-01-01 Cleanup openwrt image build and setup
2016-01-07 Docker container for mqtt2graphite
2016-01-07 Updated mqtt2graphite to allow custom port
2016-01-07 Finish image build for pi
2016-01-07 Enable squashfs inside rpi image. Doesnt boot properly using it yet.
2016-03-25 Later version of the carbon+graphite+grafana container
2016-03-25 Add a shim to reset the RTC in the MCU
2016-03-25 Program to see the ESP8266 boot codes
2016-03-25 Hack program to use the cp2102 to reprogram the esp
2016-03-26 Fix DHT build
2016-03-26 For docker 1.8
2016-03-26 Skeleton for esp gateway
2016-03-26 Fix eol
2016-03-26 Import wifi manager
2016-03-26 Working framework of ESP07 web server / wifi reset handling
2016-03-27 Yak shaving #1 - code splitting
2016-03-27 Use onboard LED to indicate wifi reset sequence
2016-03-28 Working radio monitor mode.
2016-03-30 Missed license
2016-03-30 Yak shaving
2016-03-30 Web server concurrently
2017-03-13 Shutdown the old weebly account, using github hosting now

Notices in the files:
base-station/sx1276/sx1276.cpp:
Copyright (c) 2015 Andrew McDonnell <bugs@andrewmcdonnell.net>
SentriFarm Radio Relay is free software: you can redistribute it and/or modify
it under the terms of the GNU General Public License as published by
the Free Software Foundation, either version 3 of the License, or
(at your option) any later version.
parts and their libraries:
SparkFun-Passives: Licensing: Creative Commons ShareAlike 4.0 International - https://creativecommons.org/licenses/by-sa/4.0
